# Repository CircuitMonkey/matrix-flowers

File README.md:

# matrix-flowers
Electronic art project. Vase of flowers made with seven segment LED modules.

* Matrix Flower 1
A flower made with module found on Amazon. See my proof of concept project
for the 74HC164 based module on Arduino at:
https://github.com/CircuitMonkey/hc164-2x4-led-segment-module

This flower project builds upon the proof-of-concept by making a custom
barebones Arduino PCB using the ATmega328P and allows direct soldering of the
LED modulel to that board. The board also provides mechanical mounting of a
fabricated flower stem that facilitates DC power to the module from the bottom
of the powered vase.

[YouTube: Video of the working bouquet for Matrix-1](https://youtu.be/2mtg5pHPPw4)

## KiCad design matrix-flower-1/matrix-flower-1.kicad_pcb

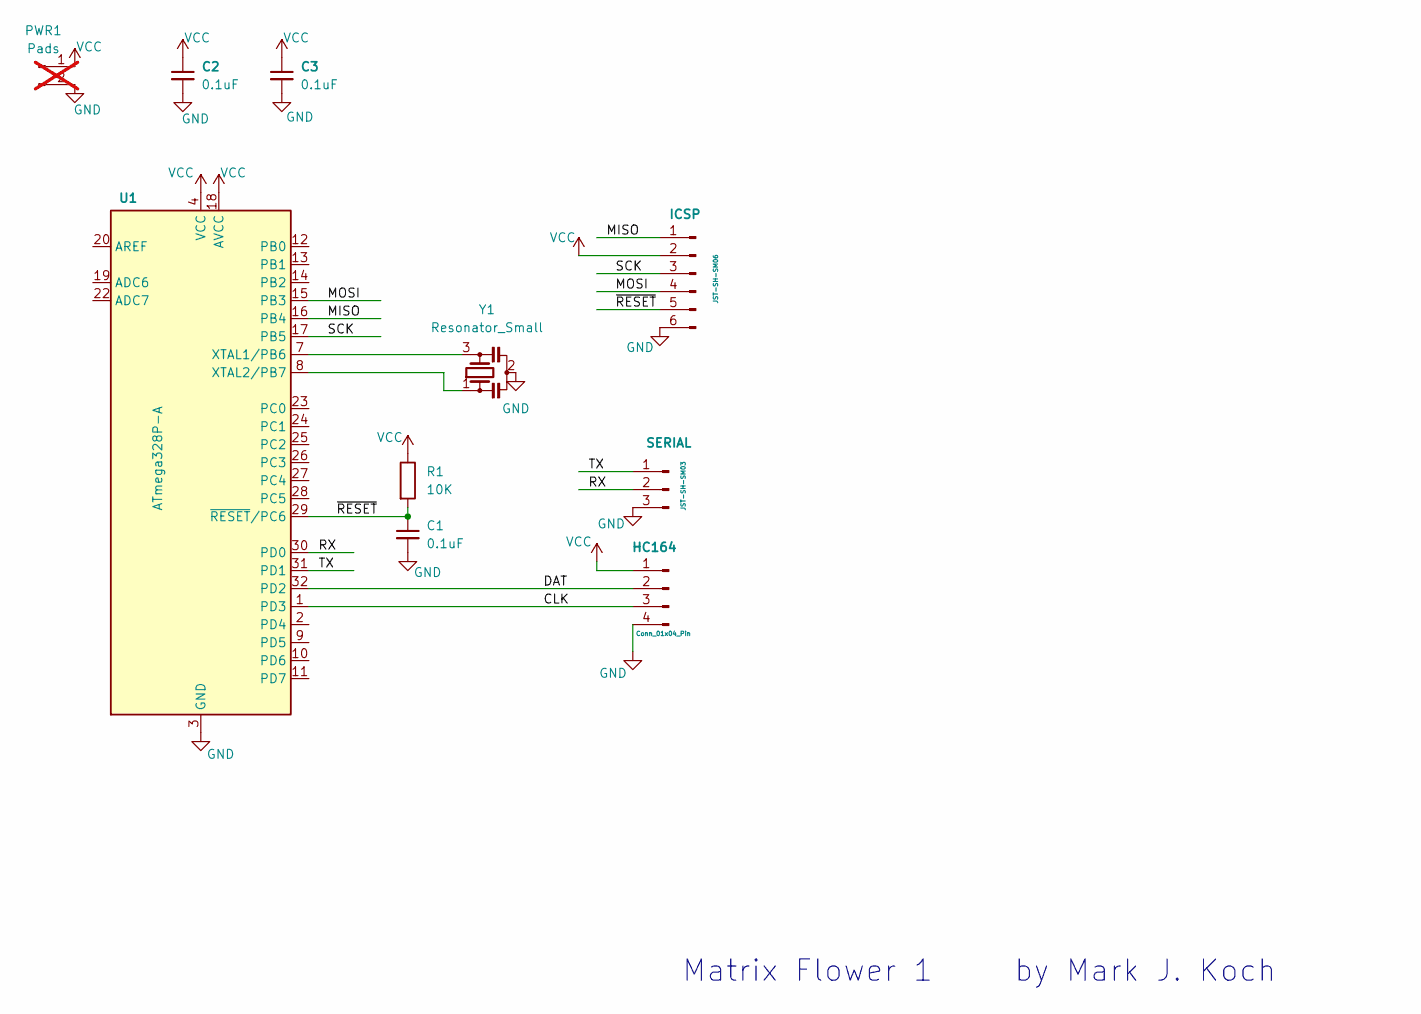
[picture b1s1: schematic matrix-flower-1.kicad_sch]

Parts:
C1, C2, C3: 0.1uF; C_0603_1608Metric_Pad1.08x0.95mm_HandSolder
HC164: Conn_01x04_Pin; PinHeader_1x04_P2.54mm_Vertical
ICSP1: JST-SH-SM06; JST_SH_SM06B-SRSS-TB_1x06-1MP_P1.00mm_Horizontal
PWR1: Pads; R_1206_3216Metric_Pad1.30x1.75mm_HandSolder; not fitted
R1: 10K; R_0603_1608Metric_Pad0.98x0.95mm_HandSolder
SERIAL1: JST-SH-SM03; JST_SH_SM03B-SRSS-TB_1x03-1MP_P1.00mm_Horizontal
U1: ATmega328P-A; TQFP-32_7x7mm_P0.8mm
Y1: Resonator_Small; Resonator_SMD_Murata_CSTxExxV-3Pin_3.0x1.1mm_HandSoldering

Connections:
/CLK: HC164.3, U1.1 (PD3)
/DAT: HC164.2, U1.32 (PD2)
/MISO: ICSP1.1, U1.16 (PB4)
/MOSI: ICSP1.4, U1.15 (PB3)
/RX: SERIAL1.2, U1.30 (PD0)
/SCK: ICSP1.3, U1.17 (PB5)
/TX: SERIAL1.1, U1.31 (PD1)
/~RESET: C1.1, ICSP1.5, R1.2, U1.29 (~RESET/PC6)
GND: C1.2, C2.2, C3.2, HC164.4, ICSP1.6, PWR1.2, SERIAL1.3, U1.3 (GND), U1.5 (GND), U1.21 (GND), Y1.2
unnamed: U1.7 (XTAL1/PB6), Y1.3
unnamed: U1.8 (XTAL2/PB7), Y1.1
VCC: C2.1, C3.1, HC164.1, ICSP1.2, PWR1.1, R1.1, U1.4 (VCC), U1.6 (VCC), U1.18 (AVCC)

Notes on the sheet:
Matrix Flower 1 by Mark J. Koch

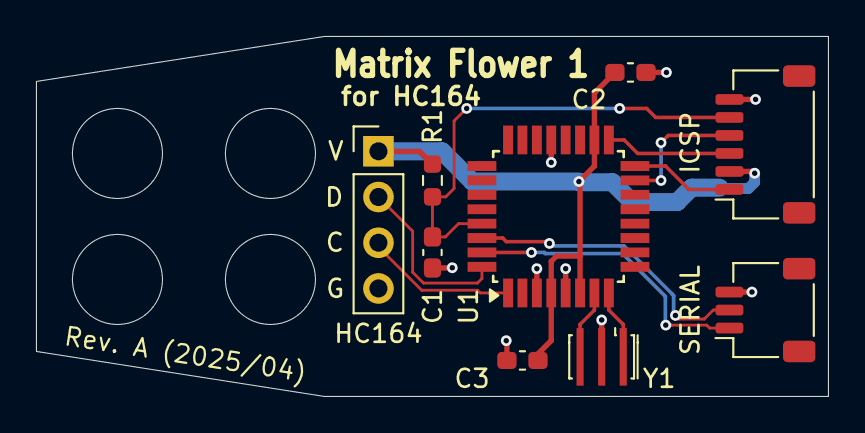
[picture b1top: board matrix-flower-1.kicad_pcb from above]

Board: 2 copper layers, 44.0 x 20.0 mm, 10 parts (1 on the bottom side), 12 nets.

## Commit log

2025-04-08 Add gerbers for matrix-flower-1-a
2025-04-08 Add KiCAD files for matrix-flower-1
2025-04-08 Update README with PCB images.
2025-04-09 Add BOM and schematic.
2025-04-09 Add code example.
2025-04-09 Update component information.
2025-05-16 Update README.md
    Add video link
